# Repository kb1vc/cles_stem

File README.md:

# cles_stem
The AttendanceBot 2000 Project

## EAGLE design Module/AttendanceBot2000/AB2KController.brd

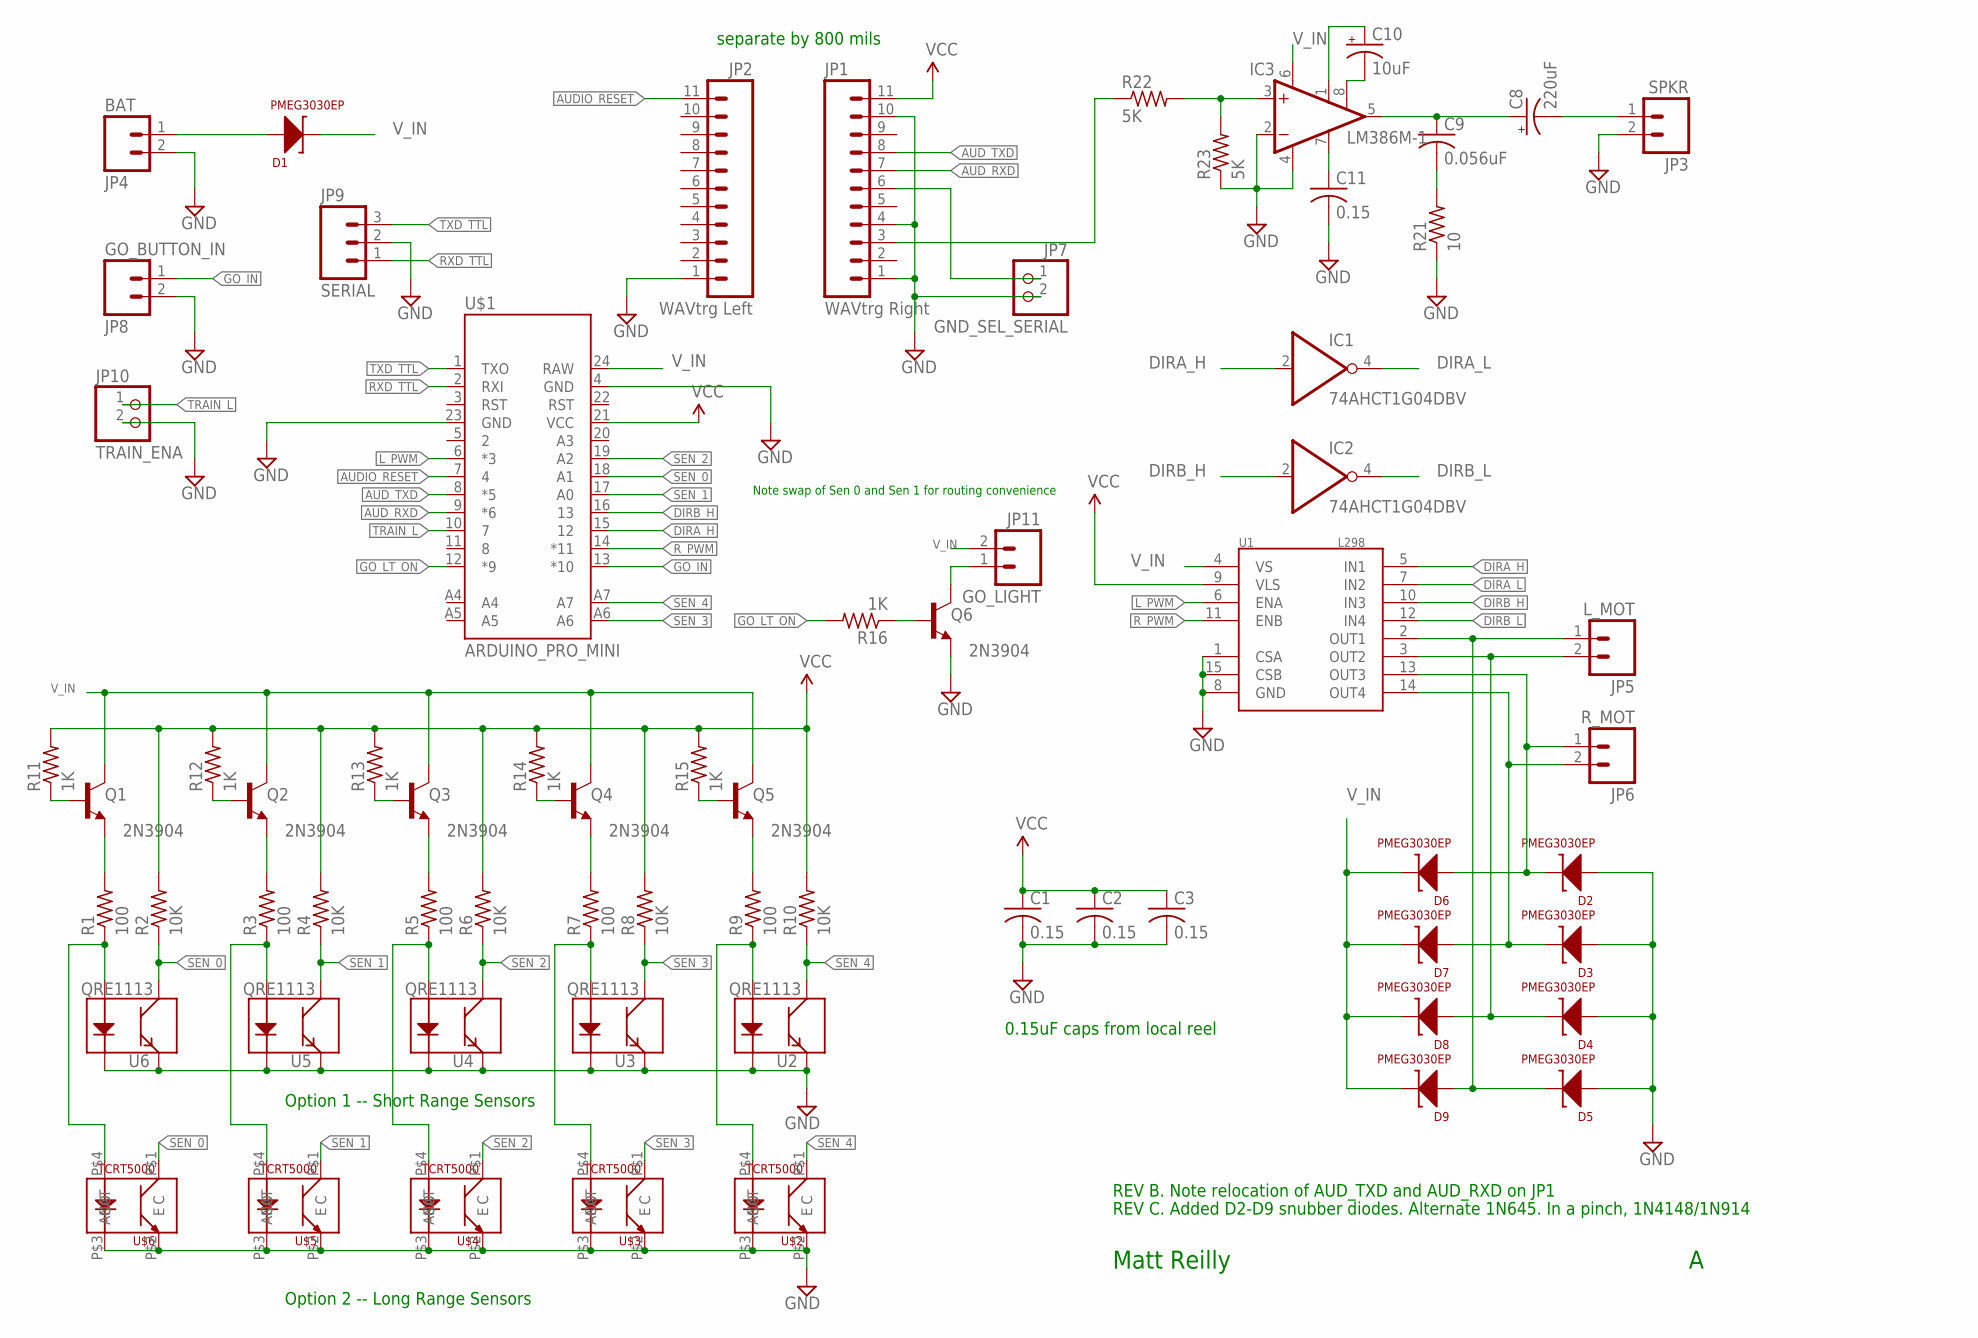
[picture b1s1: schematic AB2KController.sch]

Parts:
C1, C2, C3, C11: 0.15; C1206K
C8: 220uF; D/7343-31R
C9: 0.056uF; C1210
C10: 10uF; D/7343-31R
D1, D2, D3, D4, D5, D6, D7, D8, D9: PMEG3030EP; SOD128
IC1, IC2: 74AHCT1G04DBV; SOT23-5
IC3: LM386M-1; SO08
JP1: WAVtrg Right; 1X11
JP2: WAVtrg Left; 1X11
JP3: SPKR; SCREWTERMINAL-5MM-2
JP4: BAT; SCREWTERMINAL-5MM-2
JP5: L_MOT; SCREWTERMINAL-5MM-2
JP6: R_MOT; SCREWTERMINAL-5MM-2
JP7: GND_SEL_SERIAL; 1X02
JP8: GO_BUTTON_IN; SCREWTERMINAL-5MM-2
JP9: SERIAL; 1X03
JP10: TRAIN_ENA; 1X02
JP11: GO_LIGHT; SCREWTERMINAL-5MM-2
Q1, Q2, Q3, Q4, Q5, Q6: 2N3904; TO92
R1, R3, R5, R7, R9: 100; M1206
R2, R4, R6, R8, R10: 10K; M1206
R11, R12, R13, R14, R15, R16: 1K; M1206
R21: 10; R1210
R22, R23: 5K; R1206
U1: L298; MULTIWATT15
U2, U3, U4, U5, U6: QRE1113
U$1: ARDUINO_PRO_MINI
U$2, U$3, U$4, U$5, U$6: TCRT5000

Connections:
AUDIO_RESET: JP2.11, U$1.7 (4)
AUD_RXD: JP1.7, U$1.9 (*6)
AUD_TXD: JP1.8, U$1.8 (*5)
DIRA_H: IC1.2 (I), U1.5 (IN1), U$1.15 (12)
DIRA_L: IC1.4 (O), U1.7 (IN2)
DIRB_H: IC2.2 (I), U1.10 (IN3), U$1.16 (13)
DIRB_L: IC2.4 (O), U1.12 (IN4)
GND: C1.2, C2.2, C3.2, C11.2, D2.P$1 (A), D3.P$1 (A), D4.P$1 (A), D5.P$1 (A), IC1.3 (GND), IC2.3 (GND), IC3.2 (-IN), IC3.4 (GND), JP1.1, JP1.4, JP1.10, JP2.1, JP3.2, JP4.2, JP7.2, JP8.2, JP9.2, JP10.2, Q6.3 (E), R21.1, R23.1, U1.1 (CSA), U1.8 (GND), U1.15 (CSB), U2.2 (K), U2.4 (E), U3.2 (K), U3.4 (E), U4.2 (K), U4.4 (E), U5.2 (K), U5.4 (E), U6.2 (K), U6.4 (E), U$1.4 (GND), U$1.23 (GND), U$2.P$2 (E), U$2.P$3 (CAT), U$3.P$2 (E), U$3.P$3 (CAT), U$4.P$2 (E), U$4.P$3 (CAT), U$5.P$2 (E), U$5.P$3 (CAT), U$6.P$2 (E), U$6.P$3 (CAT)
GO_IN: JP8.1, U$1.13 (*10)
GO_LT_ON: R16.2, U$1.12 (*9)
L_PWM: U1.6 (ENA), U$1.6 (*3)
unnamed: D5.P$2 (C), D9.P$1 (A), JP5.1, U1.2 (OUT1)
unnamed: D4.P$2 (C), D8.P$1 (A), JP5.2, U1.3 (OUT2)
unnamed: D2.P$2 (C), D6.P$1 (A), JP6.1, U1.13 (OUT3)
unnamed: D3.P$2 (C), D7.P$1 (A), JP6.2, U1.14 (OUT4)
unnamed: D1.P$1 (A), JP4.1
unnamed: JP11.1, Q6.1 (C)
unnamed: R1.1, U6.1 (A), U$6.P$4 (ANO)
unnamed: R3.1, U5.1 (A), U$5.P$4 (ANO)
unnamed: Q1.3 (E), R1.2
unnamed: Q2.3 (E), R3.2
unnamed: R5.1, U4.1 (A), U$4.P$4 (ANO)
unnamed: Q3.3 (E), R5.2
unnamed: R7.1, U3.1 (A), U$3.P$4 (ANO)
unnamed: R9.1, U2.1 (A), U$2.P$4 (ANO)
unnamed: Q1.2 (B), R11.1
unnamed: IC3.3 (+IN), R22.2, R23.2
unnamed: Q2.2 (B), R12.1
unnamed: C8.+, C9.1, IC3.5 (OUT)
unnamed: C8.-, JP3.1
unnamed: C10.-, IC3.8 (GAIN)
unnamed: C9.2, R21.2
unnamed: C10.+, IC3.1 (GAIN)
unnamed: C11.1, IC3.7 (BYPASS)
unnamed: Q3.2 (B), R13.1
unnamed: Q6.2 (B), R16.1
unnamed: Q4.2 (B), R14.1
unnamed: JP1.3, R22.1
unnamed: JP1.6, JP7.1
unnamed: Q5.2 (B), R15.1
unnamed: Q4.3 (E), R7.2
unnamed: Q5.3 (E), R9.2
RXD_TTL: JP9.1, U$1.2 (RXI)
R_PWM: U1.11 (ENB), U$1.14 (*11)
SEN_0: R2.1, U6.3 (C), U$1.18 (A1), U$6.P$1 (C)
SEN_1: R4.1, U5.3 (C), U$1.17 (A0), U$5.P$1 (C)
SEN_2: R6.1, U4.3 (C), U$1.19 (A2), U$4.P$1 (C)
SEN_3: R8.1, U3.3 (C), U$1.A6, U$3.P$1 (C)
SEN_4: R10.1, U2.3 (C), U$1.A7, U$2.P$1 (C)
TRAIN_L: JP10.1, U$1.10 (7)
TXD_TTL: JP9.3, U$1.1 (TXO)
VCC: C1.1, C2.1, C3.1, IC1.5 (VCC), IC2.5 (VCC), JP1.11, R2.2, R4.2, R6.2, R8.2, R10.2, R11.2, R12.2, R13.2, R14.2, R15.2, U1.9 (VLS), U$1.21 (VCC)
V_IN: D1.P$2 (C), D6.P$2 (C), D7.P$2 (C), D8.P$2 (C), D9.P$2 (C), IC3.6 (VS), JP11.2, Q1.1 (C), Q2.1 (C), Q3.1 (C), Q4.1 (C), Q5.1 (C), U1.4 (VS), U$1.24 (RAW)

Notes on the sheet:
Option 1 -- Short Range Sensors
Option 2 -- Long Range Sensors
0.15uF caps from local reel
separate by 800 mils
Matt Reilly
Note swap of Sen 0 and Sen 1 for routing convenience
REV B. Note relocation of AUD_TXD and AUD_RXD on JP1
REV C. Added D2-D9 snubber diodes. Alternate 1N645. In a pinch, 1N4148/1N914

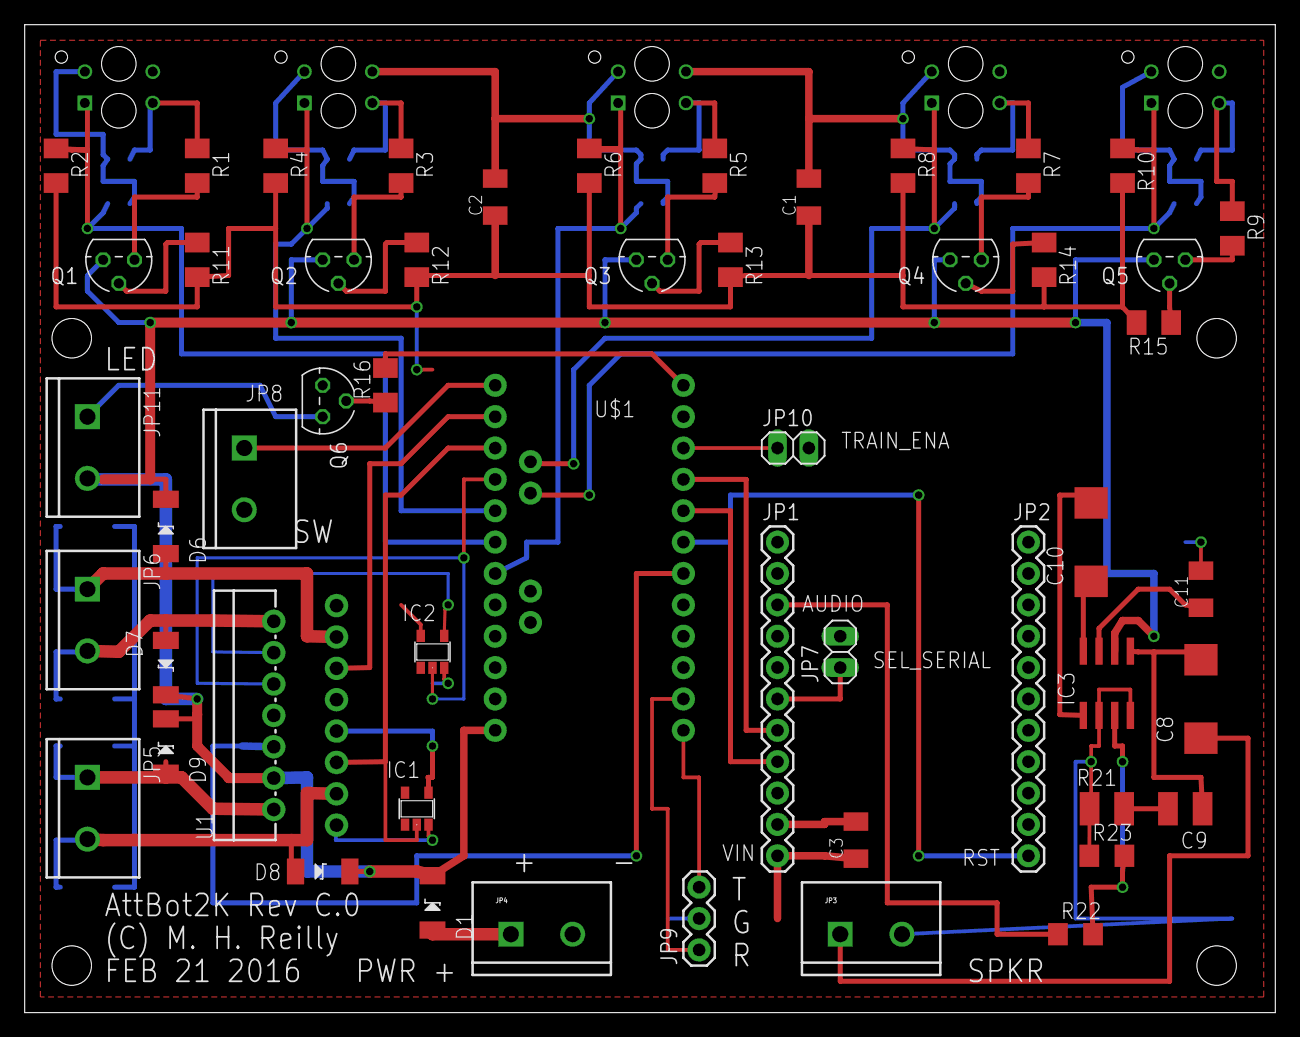
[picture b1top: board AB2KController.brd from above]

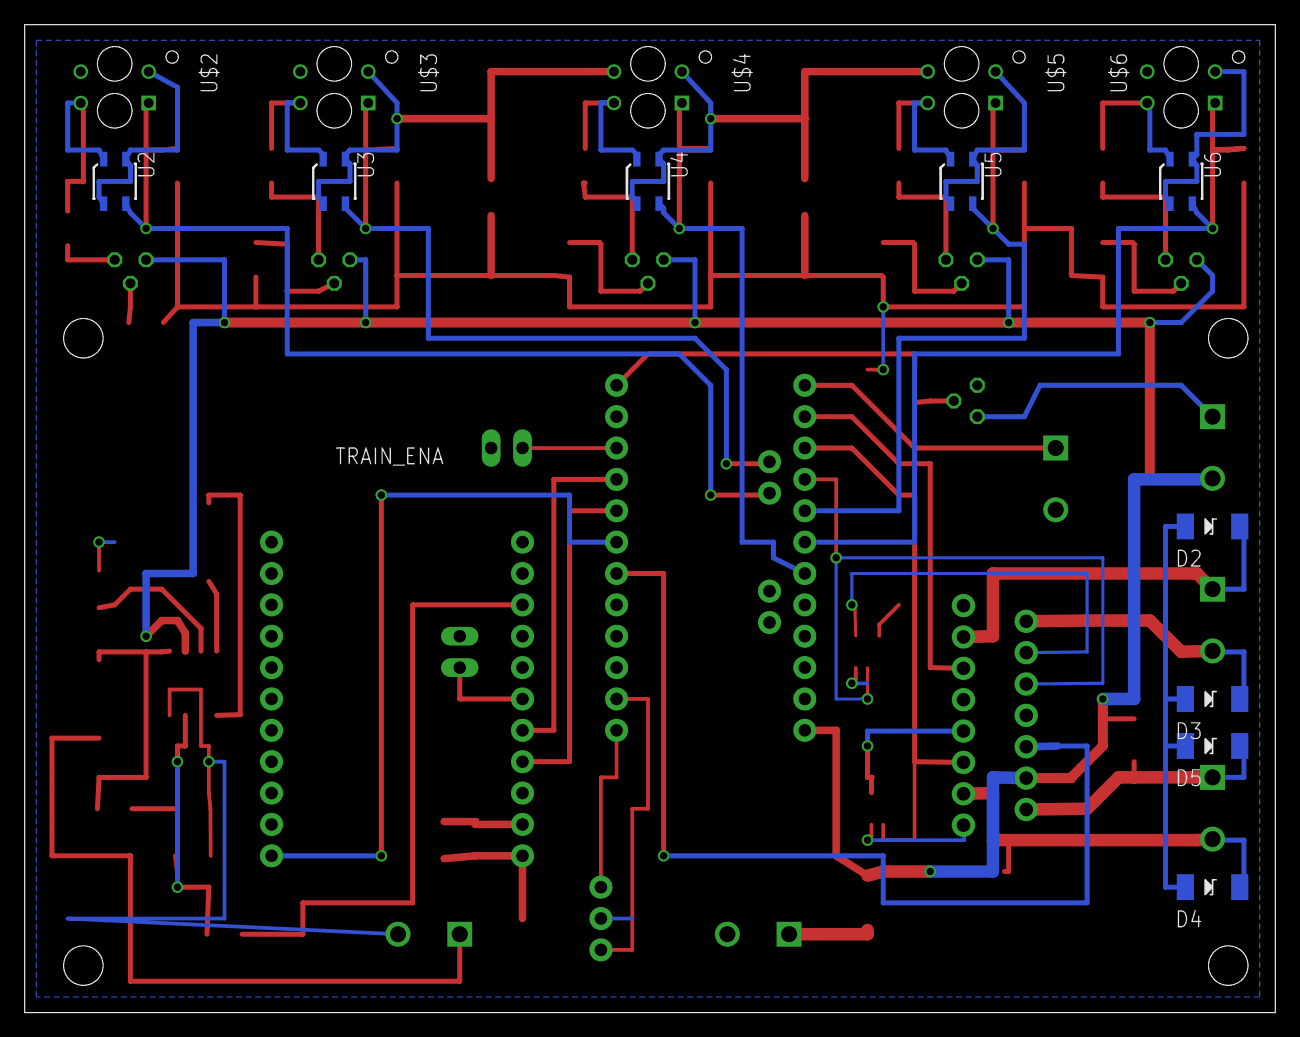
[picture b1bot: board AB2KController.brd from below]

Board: 2 copper layers, 101.3 x 80.0 mm, 67 parts (14 on the bottom side), 53 nets.

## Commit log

2016-01-17 Creating repo
2016-01-17 added controller schematic
2016-01-17 test
2016-01-18 Schematic and layout WIP.
2016-01-18 More progress on routing
2016-01-18 More layout complete
2016-01-22 Finished routing. Sleep on it for a day
2016-01-22 submitted board A0 to OSH Park
2016-01-26 Added keynote presentation
2016-01-26 more comments in pres. notes.
2016-01-30 Added animation and pix/drawings
2016-01-30 Added alice and the walk
2016-01-30 Bob, Alice, and the walk into the building.
2016-01-30 Added whiteboard brainstorming session
2016-01-30 Added sketch to thing
2016-01-31 working on movie formats
2016-01-31 Do not use convert on mac -- it produces bad pngs
2016-01-31 added PHB
2016-01-31 Fixed build scripts for Alice and Bob
2016-01-31 Fixes for build scripts
2016-01-31 something is goofy with mp4 creation.
2016-02-05 Added motor mount
2016-02-06 new version of motor mount
2016-02-09 Added test code
2016-02-09 Fixed mis-wiring of AUD_TXD and AUD_RXD in sch and board.
2016-02-10 Fixed misconnect for UG vs CS...
2016-02-13 Add soundfiles
2016-02-15 initial tests complete -- all systems work, more or less
2016-02-15 more progress -- making libs for each component.
2016-02-20 Added IR tests, fleshing out sounds and irsensors libs.
2016-02-20 updates to sound list
2016-02-21 Started to build the app.
2016-02-22 Works! Ready for demo
2016-02-22 Added snubber diodes to motor outputs.
2016-02-25 More pictures and screen captures
2016-02-25 Moved drawings
2016-02-25 More cleanup.
2016-02-25 Added new pictures -- brochures, NSBA, AASA
2016-02-27 added desk png files
2016-02-27 updated sketch 2 thing
2016-02-27 Added more sketches
2016-02-27 added spreadsheet
2016-02-27 svg to png on mac does not work well... export pngs
2016-02-27 Added bobs desktop picture.
2016-02-27 added more people
2016-02-28 Fixed robot animation
2016-02-28 Added kids animation
2016-02-28 fixed mispelling in BugReport.svg

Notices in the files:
parts and their libraries:
SparkFun-Connectors: Licensing: Creative Commons ShareAlike 4.0 International - https://creativecommons.org/licenses/by-sa/4.0
